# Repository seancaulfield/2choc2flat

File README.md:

# 2 Choc 2 Flat v1.5 and v2.1

Low profile 60% PCB designed for Choc V2 switches in hot swap sockets. Based on the Plain60-C design. Four versions are provided:

* ISO(ish) without lighting
* ANSI without lighting
* ISO(ish) with RGB per-key and underglow
* ANSI with RGB per-key and underglow (TODO)

## Features

- Compatible with QMK Firmware
- Compatible with cases supporting the GH60 layout
- LED for capslock for non-RGB versions
- Minimal layout support due to hot swap sockets
- ANSI has 64 keys; ISO(ish) has 65 (split backspace)
- Both use 2U left shift keys to squeeze in the arrow cluster

## Notes/Cautions

ISO(ish) boards will need to get a custom plate cut, as there are no
commercially available ones I've found. Files for this are included in the
`plate` directory within the project directory for each ISO version.

The layout used is the 2U left shift 60% layout, which allows the arrow cluster
to be included. Check your keycap compatibility before using.

## Bill of materials (BOM)

For all versions:

* 64-65 Kailh Choc hot swap sockets (depending on variant)
* 64-65 SOD-323 diodes
* Gateron low-profile stabilizers (1 6.25U, 2-3 2U)
* Plate compatible with Gateron low-profile stabilizers
  * any Cherry plate mount stabilizer compatible should do
  * e.g. [this one at Adafruit](https://www.adafruit.com/product/5133)
  * DXF/SVG/EPS files for ISOish plates are in the project directories for them
* Waveshare RP2040 Tiny, which has the USB port attached via FFC
  * [Amazon](https://www.amazon.com/dp/B0C4FC84V9)
  * [Aliexpress](https://www.aliexpress.us/item/3256806201372671.html)

For non-RGB versions, you will also need:

* 2 1206 reverse mount LEDs (for capslock)
* 2 0603 ~470ohm resistors (for capslock LEDs)

For RGB versions, you will also need:

* 64-65 SK6812-E reverse mount NeoPixel RGB LEDs
* 16 NeoPixel Nano 2020 RGB LEDs
* 1 SN74LVC2G125DCT SSOP-8 buffer chip
* 0603 1u(ish) X5R capacitor

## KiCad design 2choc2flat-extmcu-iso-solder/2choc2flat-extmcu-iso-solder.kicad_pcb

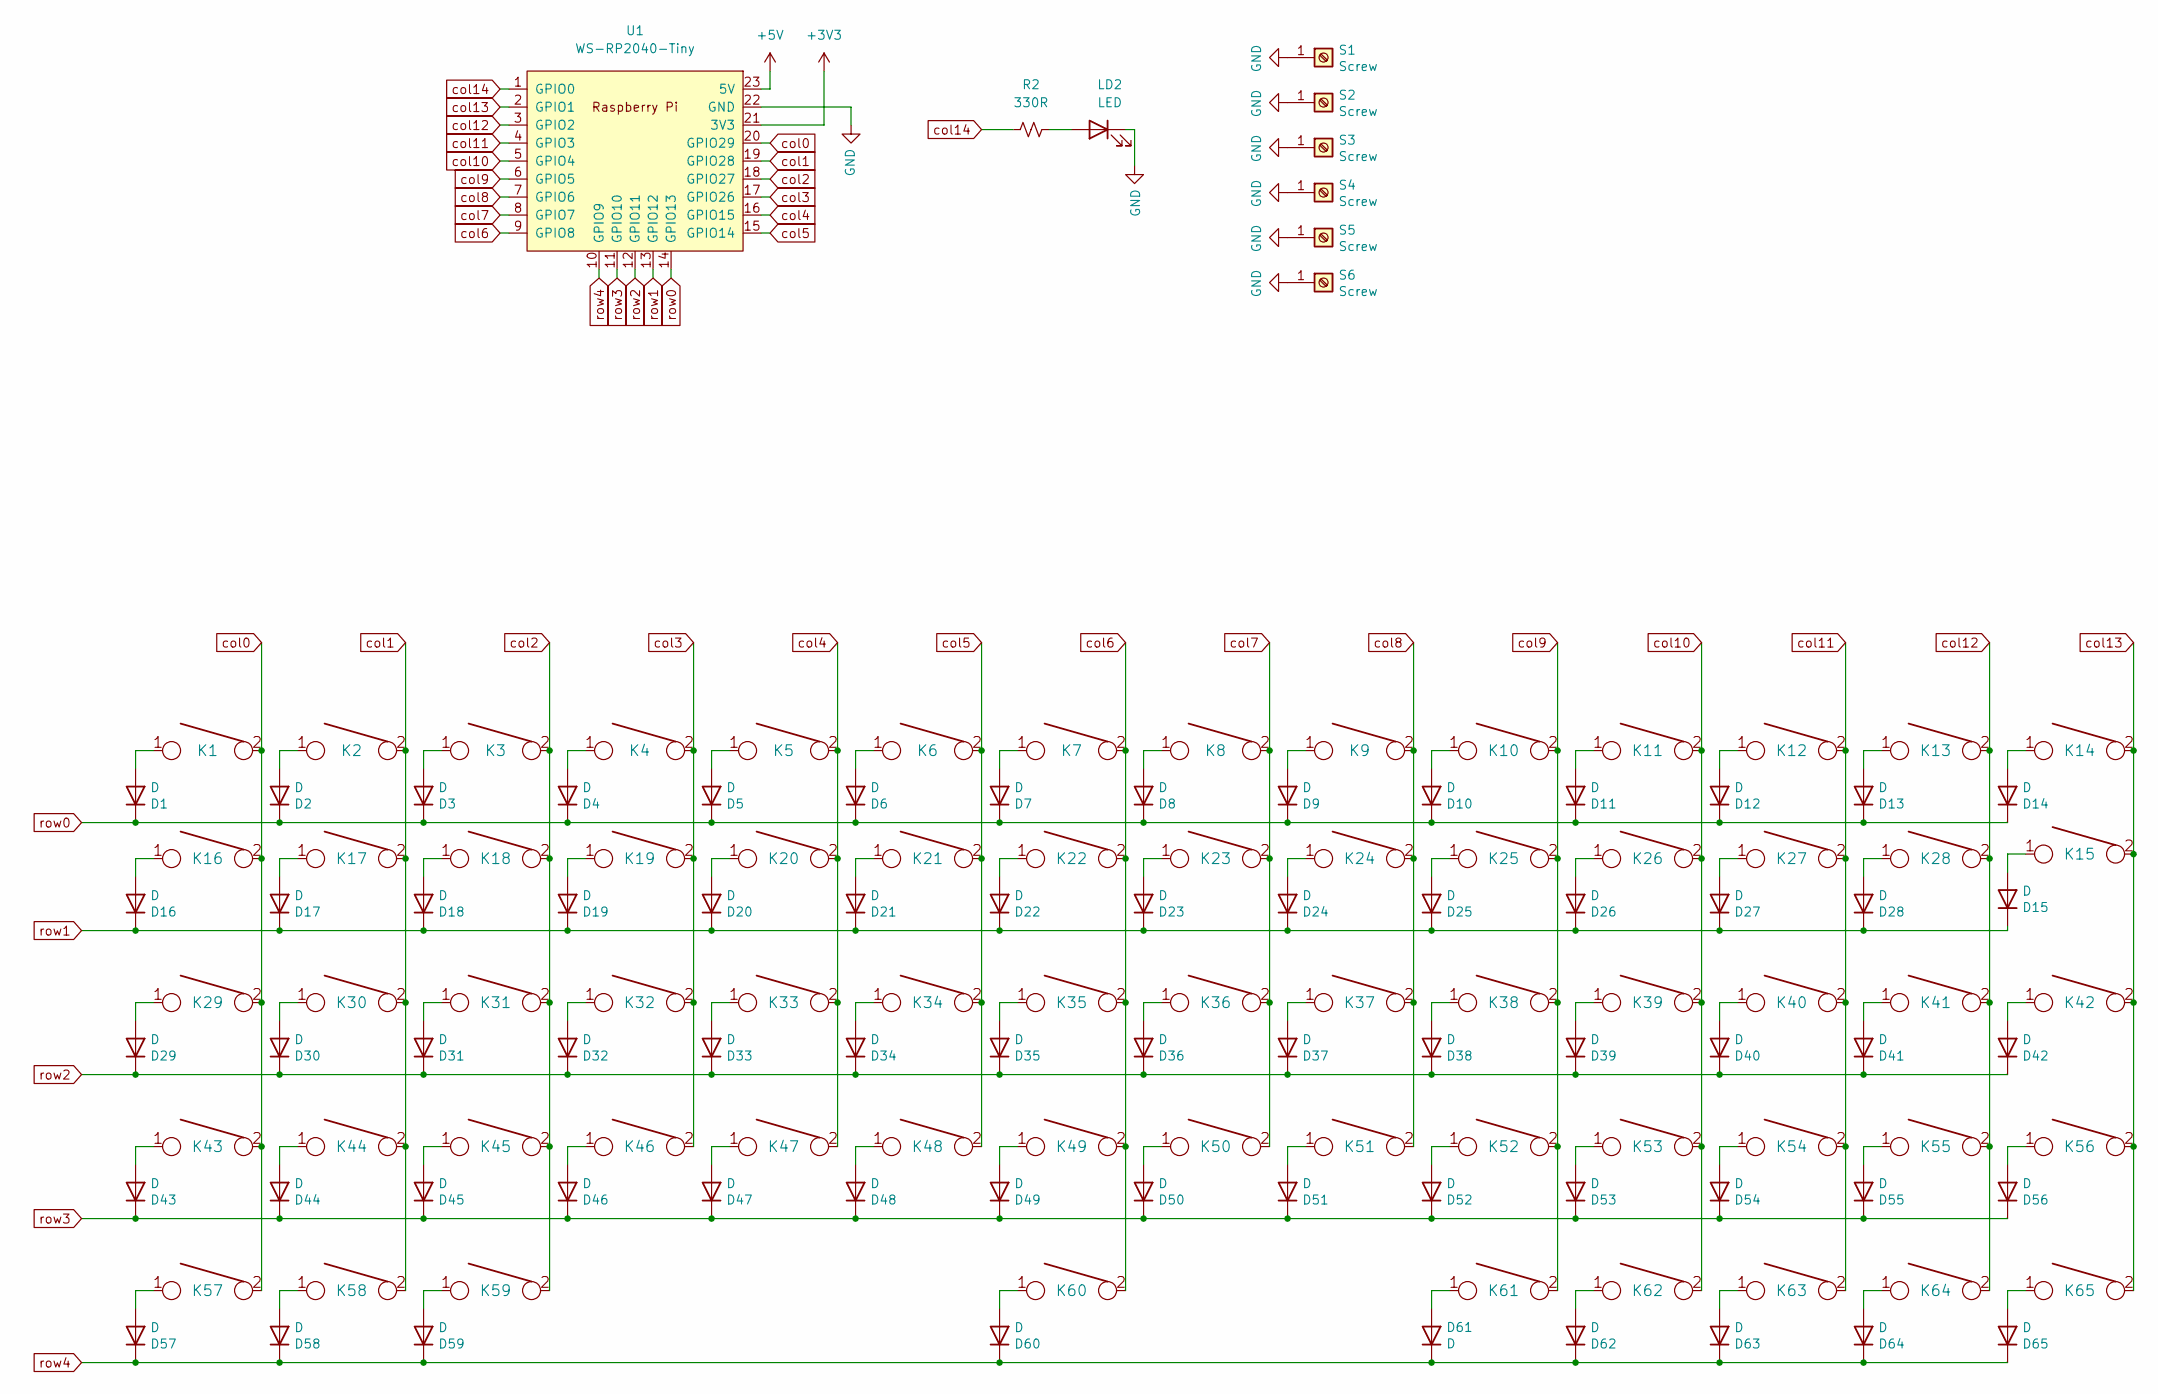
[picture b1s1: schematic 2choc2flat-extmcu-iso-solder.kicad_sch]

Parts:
D1, D2, D3, D4, D5, D6, D7, D8, D9, D10, D11, D12, D13, D14, D15, D16, D17, D18, D19, D20, D21, D22, D23, D24, D25, D26, D27, D28, D29, D30, D31, D32, D33, D34, D35, D36, D37, D38, D39, D40, D41, D42, D43, D44, D45, D46, D47, D48, D49, D50, D51, D52, D53, D54, D55, D56, D57, D58, D59, D60, D61, D62, D63, D64, D65: D; D_SOD-323_HandSoldering
K1, K2, K3, K4, K5, K6, K7, K8, K9, K10, K11, K12, K13, K14, K15, K17, K18, K19, K20, K21, K22, K23, K24, K25, K26, K27, K28, K30, K31, K32, K33, K34, K35, K36, K37, K38, K39, K40, K41, K44, K45, K46, K47, K48, K49, K50, K51, K52, K53, K54, K55, K56, K61, K62, K63, K64, K65: KEYSW; SW_Soldered_Kailh_Choc_V2_1.00u
K16: KEYSW; SW_Soldered_Kailh_Choc_V2_1.50u
K29: KEYSW; SW_Soldered_Kailh_Choc_V2_1.75u
K42: KEYSW; SW_Soldered_Kailh_Choc_V2_ISOEnter_West_Gateron_LP_Stabs
K43: KEYSW; SW_Soldered_Kailh_Choc_V2_2.00u_0deg_Gateron_LP_Stabs
K57, K58, K59: KEYSW; SW_Soldered_Kailh_Choc_V2_1.25u
K60: KEYSW; SW_Soldered_Kailh_Choc_V2_6.25u
LD2: LED; LED_1206_3216Metric_ReverseMount_Hole1.8x2.4mm
R2: 330R; R_0603_1608Metric
S1, S2, S6: Screw; 3_5x2.5mm
S3: Screw; MountingHole_2.2mm_M2_Pad_TopOnly
S4, S5: Screw; 8x3.5_7x2.5mm
U1: WS-RP2040-Tiny; WAVESHARE_RP2040_TINY_SLIM

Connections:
+3V3: U1.21 (3V3)
+5V: U1.23 (5V)
GND: LD2.1 (K), S1.1, S2.1, S3.1, S4.1, S5.1, S6.1, U1.22 (GND)
unnamed: D1.2 (A), K1.1
unnamed: D2.2 (A), K2.1
unnamed: D3.2 (A), K3.1
unnamed: D4.2 (A), K4.1
unnamed: D5.2 (A), K5.1
unnamed: D6.2 (A), K6.1
unnamed: D7.2 (A), K7.1
unnamed: D8.2 (A), K8.1
unnamed: D9.2 (A), K9.1
unnamed: D10.2 (A), K10.1
unnamed: D11.2 (A), K11.1
unnamed: D12.2 (A), K12.1
unnamed: D13.2 (A), K13.1
unnamed: D14.2 (A), K14.1
unnamed: D15.2 (A), K15.1
unnamed: D16.2 (A), K16.1
unnamed: D17.2 (A), K17.1
unnamed: D18.2 (A), K18.1
unnamed: D19.2 (A), K19.1
unnamed: D20.2 (A), K20.1
unnamed: D21.2 (A), K21.1
unnamed: D22.2 (A), K22.1
unnamed: D23.2 (A), K23.1
unnamed: D24.2 (A), K24.1
unnamed: D25.2 (A), K25.1
unnamed: D26.2 (A), K26.1
unnamed: D27.2 (A), K27.1
unnamed: D28.2 (A), K28.1
unnamed: D29.2 (A), K29.1
unnamed: D30.2 (A), K30.1
unnamed: D31.2 (A), K31.1
unnamed: D32.2 (A), K32.1
unnamed: D33.2 (A), K33.1
unnamed: D34.2 (A), K34.1
unnamed: D35.2 (A), K35.1
unnamed: D36.2 (A), K36.1
unnamed: D37.2 (A), K37.1
unnamed: D38.2 (A), K38.1
unnamed: D39.2 (A), K39.1
unnamed: D40.2 (A), K40.1
unnamed: D41.2 (A), K41.1
unnamed: D42.2 (A), K42.1
unnamed: D43.2 (A), K43.1
unnamed: D44.2 (A), K44.1
unnamed: D45.2 (A), K45.1
unnamed: D46.2 (A), K46.1
unnamed: D47.2 (A), K47.1
unnamed: D48.2 (A), K48.1
unnamed: D49.2 (A), K49.1
unnamed: D50.2 (A), K50.1
unnamed: D51.2 (A), K51.1
unnamed: D52.2 (A), K52.1
unnamed: D53.2 (A), K53.1
unnamed: D54.2 (A), K54.1
unnamed: D55.2 (A), K55.1
unnamed: D56.2 (A), K56.1
unnamed: D57.2 (A), K57.1
unnamed: D58.2 (A), K58.1
unnamed: D59.2 (A), K59.1
unnamed: D60.2 (A), K60.1
unnamed: D61.2 (A), K61.1
unnamed: D62.2 (A), K62.1
unnamed: D63.2 (A), K63.1
unnamed: D64.2 (A), K64.1
unnamed: D65.2 (A), K65.1
unnamed: LD2.2 (A), R2.2
col0: K1.2, K16.2, K29.2, K43.2, K57.2, U1.20 (GPIO29)
col1: K2.2, K17.2, K30.2, K44.2, K58.2, U1.19 (GPIO28)
col2: K3.2, K18.2, K31.2, K45.2, K59.2, U1.18 (GPIO27)
col3: K4.2, K19.2, K32.2, K46.2, U1.17 (GPIO26)
col4: K5.2, K20.2, K33.2, K47.2, U1.16 (GPIO15)
col5: K6.2, K21.2, K34.2, K48.2, U1.15 (GPIO14)
col6: K7.2, K22.2, K35.2, K49.2, K60.2, U1.9 (GPIO8)
col7: K8.2, K23.2, K36.2, K50.2, U1.8 (GPIO7)
col8: K9.2, K24.2, K37.2, K51.2, U1.7 (GPIO6)
col9: K10.2, K25.2, K38.2, K52.2, K61.2, U1.6 (GPIO5)
col10: K11.2, K26.2, K39.2, K53.2, K62.2, U1.5 (GPIO4)
col11: K12.2, K27.2, K40.2, K54.2, K63.2, U1.4 (GPIO3)
col12: K13.2, K28.2, K41.2, K55.2, K64.2, U1.3 (GPIO2)
col13: K14.2, K15.2, K42.2, K56.2, K65.2, U1.2 (GPIO1)
col14: R2.1, U1.1 (GPIO0)
row0: D1.1 (K), D2.1 (K), D3.1 (K), D4.1 (K), D5.1 (K), D6.1 (K), D7.1 (K), D8.1 (K), D9.1 (K), D10.1 (K), D11.1 (K), D12.1 (K), D13.1 (K), D14.1 (K), U1.14 (GPIO13)
row1: D15.1 (K), D16.1 (K), D17.1 (K), D18.1 (K), D19.1 (K), D20.1 (K), D21.1 (K), D22.1 (K), D23.1 (K), D24.1 (K), D25.1 (K), D26.1 (K), D27.1 (K), D28.1 (K), U1.13 (GPIO12)
row2: D29.1 (K), D30.1 (K), D31.1 (K), D32.1 (K), D33.1 (K), D34.1 (K), D35.1 (K), D36.1 (K), D37.1 (K), D38.1 (K), D39.1 (K), D40.1 (K), D41.1 (K), D42.1 (K), U1.12 (GPIO11)
row3: D43.1 (K), D44.1 (K), D45.1 (K), D46.1 (K), D47.1 (K), D48.1 (K), D49.1 (K), D50.1 (K), D51.1 (K), D52.1 (K), D53.1 (K), D54.1 (K), D55.1 (K), D56.1 (K), U1.11 (GPIO10)
row4: D57.1 (K), D58.1 (K), D59.1 (K), D60.1 (K), D61.1 (K), D62.1 (K), D63.1 (K), D64.1 (K), D65.1 (K), U1.10 (GPIO9)

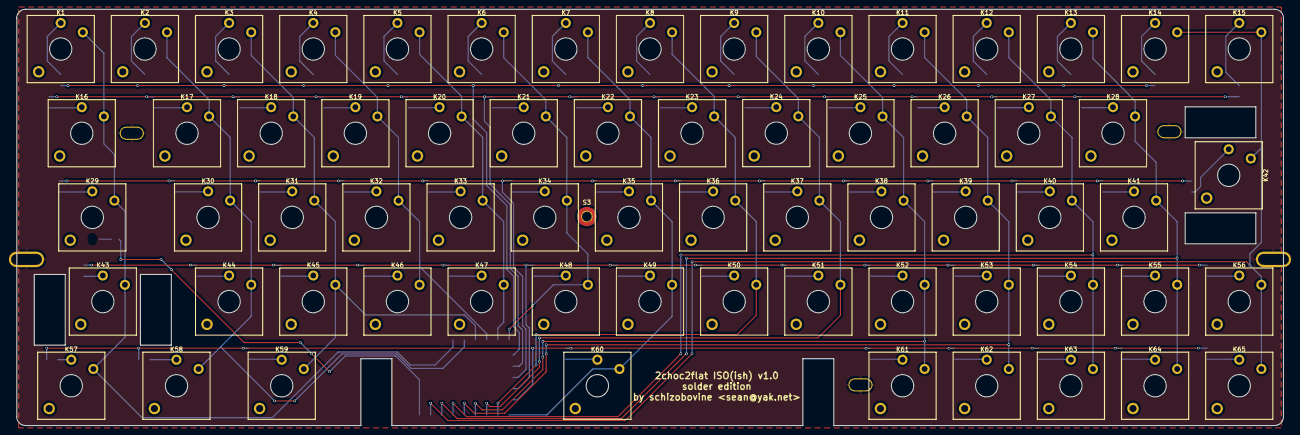
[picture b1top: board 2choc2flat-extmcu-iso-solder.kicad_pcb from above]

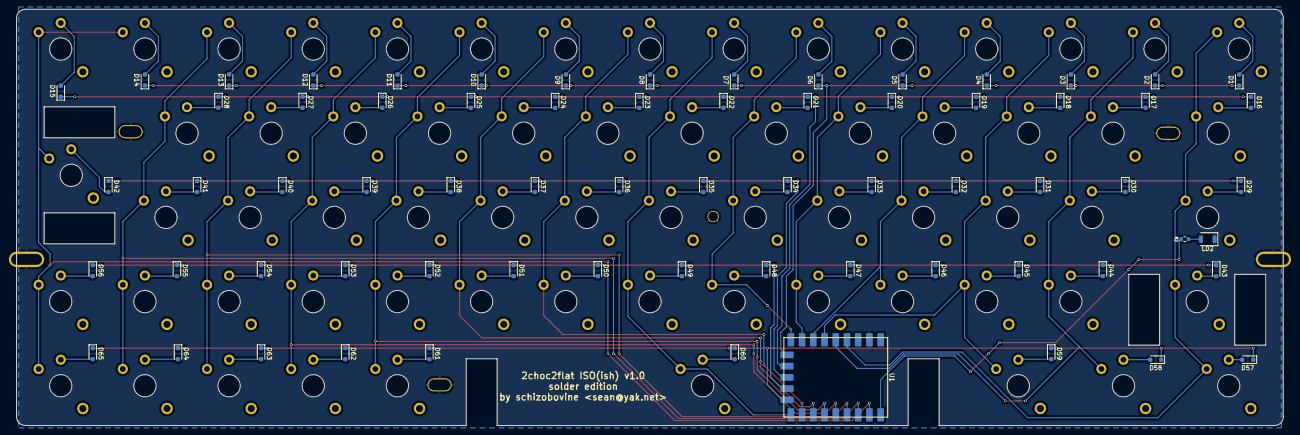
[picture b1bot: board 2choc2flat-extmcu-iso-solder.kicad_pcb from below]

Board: 2 copper layers, 286.7 x 94.2 mm, 139 parts (68 on the bottom side), 87 nets.

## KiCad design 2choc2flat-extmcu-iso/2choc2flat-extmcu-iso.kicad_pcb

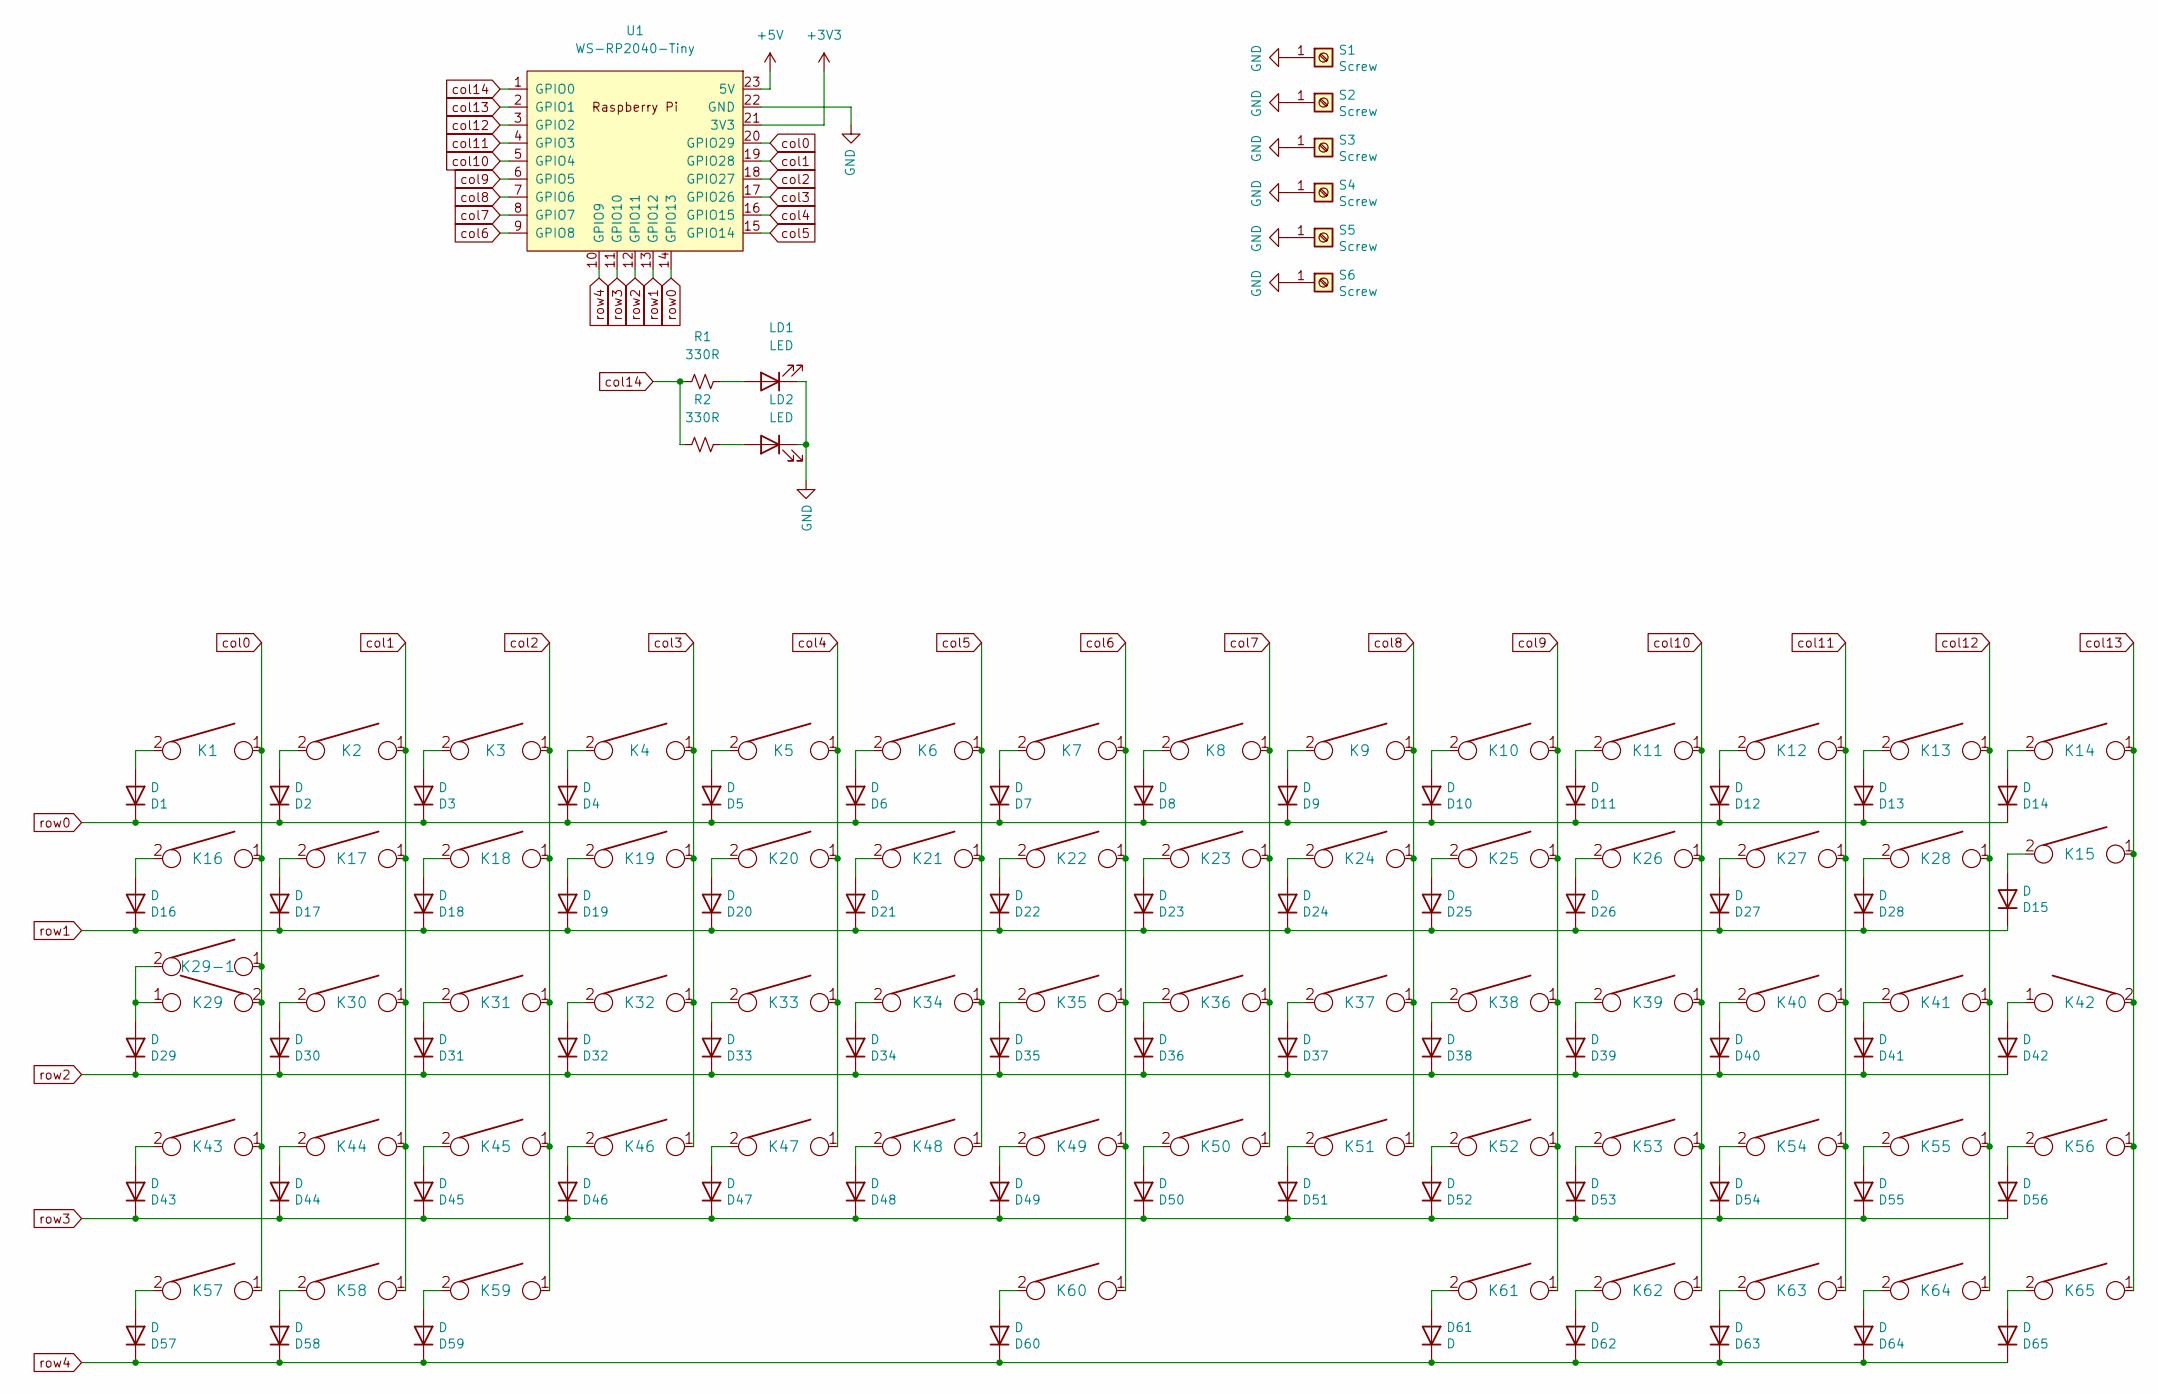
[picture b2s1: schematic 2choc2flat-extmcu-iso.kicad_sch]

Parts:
D1, D2, D3, D4, D5, D6, D7, D8, D9, D10, D11, D12, D13, D14, D15, D16, D17, D18, D19, D20, D21, D22, D23, D24, D25, D26, D27, D28, D29, D30, D31, D32, D33, D34, D35, D36, D37, D38, D39, D40, D41, D42, D43, D44, D45, D46, D47, D48, D49, D50, D51, D52, D53, D54, D55, D56, D57, D58, D59, D60, D61, D62, D63, D64, D65: D; D_SOD-323_HandSoldering
K1, K2, K3, K4, K5, K6, K7, K8, K9, K10, K11, K12, K13, K14, K15, K17, K18, K19, K20, K21, K22, K23, K24, K25, K26, K27, K28, K30, K31, K32, K33, K34, K35, K36, K37, K38, K39, K40, K41, K44, K45, K46, K47, K48, K49, K50, K51, K52, K53, K54, K55, K56, K61, K62, K63, K64, K65: KEYSW; SW_Hotswap_Kailh_Choc_V2_1.00u
K16: KEYSW; SW_Hotswap_Kailh_Choc_V2_1.50u
K29: KEYSW; SW_Hotswap_Kailh_Choc_V2_1.75u
K29-1, K57, K58, K59: KEYSW; SW_Hotswap_Kailh_Choc_V2_1.25u
K42: KEYSW; SW_Hotswap_Kailh_Choc_V2_ISOEnter_West_Gateron_LP_Stabs
K43: KEYSW; SW_Hotswap_Kailh_Choc_V2_2.00u_90deg_Gateron_LP_Stabs
K60: KEYSW; SW_Hotswap_Kailh_Choc_V2_6.25u
LD1, LD2: LED; LED_1206_3216Metric_ReverseMount_Hole1.8x2.4mm
R1, R2: 330R; R_0603_1608Metric
S1, S2, S6: Screw; 3_5x2.5mm
S3: Screw; MountingHole_2.2mm_M2_Pad_TopOnly
S4, S5: Screw; 8x3.5_7x2.5mm
U1: WS-RP2040-Tiny; WAVESHARE_RP2040_TINY

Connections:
+3V3: U1.21 (3V3)
+5V: U1.23 (5V)
GND: LD1.1 (K), LD2.1 (K), S1.1, S2.1, S3.1, S4.1, S5.1, S6.1, U1.22 (GND)
unnamed: D1.2 (A), K1.2
unnamed: D2.2 (A), K2.2
unnamed: D3.2 (A), K3.2
unnamed: D4.2 (A), K4.2
unnamed: D5.2 (A), K5.2
unnamed: D6.2 (A), K6.2
unnamed: D7.2 (A), K7.2
unnamed: D8.2 (A), K8.2
unnamed: D9.2 (A), K9.2
unnamed: D10.2 (A), K10.2
unnamed: D11.2 (A), K11.2
unnamed: D12.2 (A), K12.2
unnamed: D13.2 (A), K13.2
unnamed: D14.2 (A), K14.2
unnamed: D15.2 (A), K15.2
unnamed: D16.2 (A), K16.2
unnamed: D17.2 (A), K17.2
unnamed: D18.2 (A), K18.2
unnamed: D19.2 (A), K19.2
unnamed: D20.2 (A), K20.2
unnamed: D21.2 (A), K21.2
unnamed: D22.2 (A), K22.2
unnamed: D23.2 (A), K23.2
unnamed: D24.2 (A), K24.2
unnamed: D25.2 (A), K25.2
unnamed: D26.2 (A), K26.2
unnamed: D27.2 (A), K27.2
unnamed: D28.2 (A), K28.2
unnamed: D29.2 (A), K29.1, K29-1.2
unnamed: D30.2 (A), K30.2
unnamed: D31.2 (A), K31.2
unnamed: D32.2 (A), K32.2
unnamed: D33.2 (A), K33.2
unnamed: D34.2 (A), K34.2
unnamed: D35.2 (A), K35.2
unnamed: D36.2 (A), K36.2
unnamed: D37.2 (A), K37.2
unnamed: D38.2 (A), K38.2
unnamed: D39.2 (A), K39.2
unnamed: D40.2 (A), K40.2
unnamed: D41.2 (A), K41.2
unnamed: D42.2 (A), K42.1
unnamed: D43.2 (A), K43.2
unnamed: D44.2 (A), K44.2
unnamed: D45.2 (A), K45.2
unnamed: D46.2 (A), K46.2
unnamed: D47.2 (A), K47.2
unnamed: D48.2 (A), K48.2
unnamed: D49.2 (A), K49.2
unnamed: D50.2 (A), K50.2
unnamed: D51.2 (A), K51.2
unnamed: D52.2 (A), K52.2
unnamed: D53.2 (A), K53.2
unnamed: D54.2 (A), K54.2
unnamed: D55.2 (A), K55.2
unnamed: D56.2 (A), K56.2
unnamed: D57.2 (A), K57.2
unnamed: D58.2 (A), K58.2
unnamed: D59.2 (A), K59.2
unnamed: D60.2 (A), K60.2
unnamed: D61.2 (A), K61.2
unnamed: D62.2 (A), K62.2
unnamed: D63.2 (A), K63.2
unnamed: D64.2 (A), K64.2
unnamed: D65.2 (A), K65.2
unnamed: LD1.2 (A), R1.2
unnamed: LD2.2 (A), R2.2
col0: K1.1, K16.1, K29.2, K29-1.1, K43.1, K57.1, U1.20 (GPIO29)
col1: K2.1, K17.1, K30.1, K44.1, K58.1, U1.19 (GPIO28)
col2: K3.1, K18.1, K31.1, K45.1, K59.1, U1.18 (GPIO27)
col3: K4.1, K19.1, K32.1, K46.1, U1.17 (GPIO26)
col4: K5.1, K20.1, K33.1, K47.1, U1.16 (GPIO15)
col5: K6.1, K21.1, K34.1, K48.1, U1.15 (GPIO14)
col6: K7.1, K22.1, K35.1, K49.1, K60.1, U1.9 (GPIO8)
col7: K8.1, K23.1, K36.1, K50.1, U1.8 (GPIO7)
col8: K9.1, K24.1, K37.1, K51.1, U1.7 (GPIO6)
col9: K10.1, K25.1, K38.1, K52.1, K61.1, U1.6 (GPIO5)
col10: K11.1, K26.1, K39.1, K53.1, K62.1, U1.5 (GPIO4)
col11: K12.1, K27.1, K40.1, K54.1, K63.1, U1.4 (GPIO3)
col12: K13.1, K28.1, K41.1, K55.1, K64.1, U1.3 (GPIO2)
col13: K14.1, K15.1, K42.2, K56.1, K65.1, U1.2 (GPIO1)
col14: R1.1, R2.1, U1.1 (GPIO0)
row0: D1.1 (K), D2.1 (K), D3.1 (K), D4.1 (K), D5.1 (K), D6.1 (K), D7.1 (K), D8.1 (K), D9.1 (K), D10.1 (K), D11.1 (K), D12.1 (K), D13.1 (K), D14.1 (K), U1.14 (GPIO13)
row1: D15.1 (K), D16.1 (K), D17.1 (K), D18.1 (K), D19.1 (K), D20.1 (K), D21.1 (K), D22.1 (K), D23.1 (K), D24.1 (K), D25.1 (K), D26.1 (K), D27.1 (K), D28.1 (K), U1.13 (GPIO12)
row2: D29.1 (K), D30.1 (K), D31.1 (K), D32.1 (K), D33.1 (K), D34.1 (K), D35.1 (K), D36.1 (K), D37.1 (K), D38.1 (K), D39.1 (K), D40.1 (K), D41.1 (K), D42.1 (K), U1.12 (GPIO11)
row3: D43.1 (K), D44.1 (K), D45.1 (K), D46.1 (K), D47.1 (K), D48.1 (K), D49.1 (K), D50.1 (K), D51.1 (K), D52.1 (K), D53.1 (K), D54.1 (K), D55.1 (K), D56.1 (K), U1.11 (GPIO10)
row4: D57.1 (K), D58.1 (K), D59.1 (K), D60.1 (K), D61.1 (K), D62.1 (K), D63.1 (K), D64.1 (K), D65.1 (K), U1.10 (GPIO9)

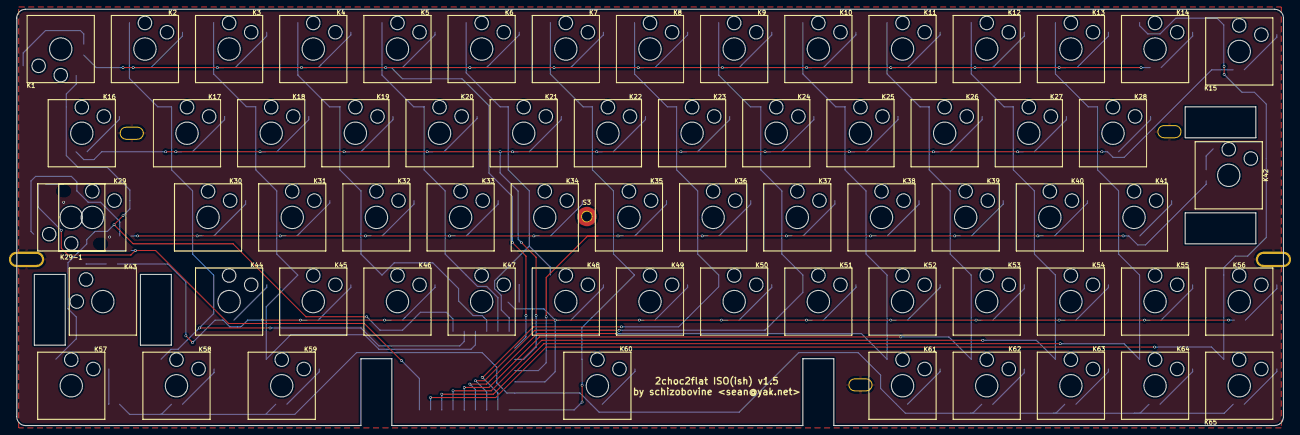
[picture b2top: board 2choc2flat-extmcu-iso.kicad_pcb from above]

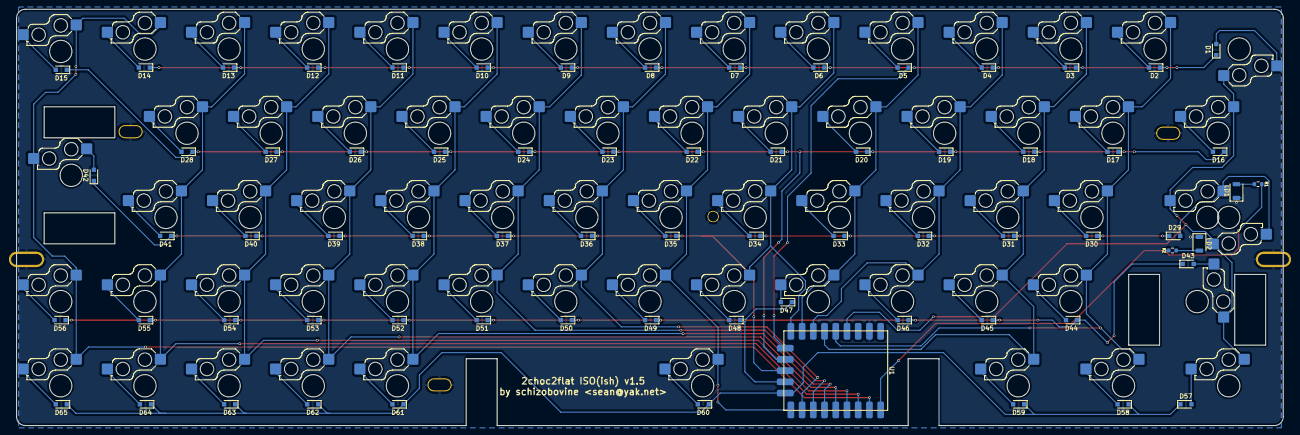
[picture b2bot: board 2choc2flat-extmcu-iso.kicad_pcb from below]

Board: 2 copper layers, 286.7 x 94.2 mm, 142 parts (70 on the bottom side), 88 nets.

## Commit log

2024-08-23 rename files for external mcu version
2024-08-24 lshift stab support
2024-08-24 pure ISO-ish version
2024-08-25 small board to test 2U stabilizer
2024-08-25 resize to save costs
2024-08-26 ansi version
2024-08-30 make ISO 64 2u left shift layout
2024-08-30 fix stab orientation to plate
2024-08-30 rejigger stabs to work with plates
2024-09-06 update readme to reflect current project
2024-09-08 wip attempting rerouting
2024-09-08 routing complete
2024-09-09 relayout using MCU with FFC USB
2024-09-09 blah
2024-09-09 wip renaming stuff
2024-09-09 rerouted, capslock light
2024-09-15 rev 1.3 layouts
2024-09-15 remove gerbers output file
2024-09-16 add second caps led, minor tweaks
2024-09-17 remove autosave file
2024-09-17 remove old files, update readme
2024-09-18 committing for foam SVGs
2024-09-19 whoops wip
2024-09-19 version 1.4 with foam layers on eco1 and eco2
2024-09-19 wip v1.4 ansi
2024-09-19 revision 1.5 bothering to use the castellated pads
2024-09-24 v1.5 ANSI with SMD rp2040 tiny
2024-09-26 wip adding RGB lighting
2024-09-26 add plotted schematics for ref and update readme
2024-09-28 wip adding lighting
2024-09-30 version 2.0 with RGB backlighting and underglow
2024-10-01 add schematics for 2.0 version
2024-10-01 rename foam files to include version
2024-10-01 v2.1 few LEDs out of alignment
2024-10-01 foam for v2.1 build
2024-10-01 remove tester board
2024-10-02 split out RGB versions into own dirs in prep to restore non-RGB versions
2024-10-02 add files for ISOish plate
2024-10-02 update readme with RGB and other info
2024-10-02 restore non-RGB versions from history into separate dirs
2024-10-02 symlink to plate dir since they're the same across the two version
2024-10-02 update library
2024-10-02 ISOish solderable version with the 3rd pin anchor
2024-10-10 more tweaks to foam layout
2024-10-10 redo underglow because i failed to map the pads correctly
2024-10-10 solderable version
2024-10-10 ignore kicad lockfiles
2024-10-16 fixing more fuckups
2024-10-22 yet another revision to fix footprints
2024-11-04 update solder foam and RGB schematic
2024-11-04 update ANSI for foam
2024-11-04 no longer going to do this one
